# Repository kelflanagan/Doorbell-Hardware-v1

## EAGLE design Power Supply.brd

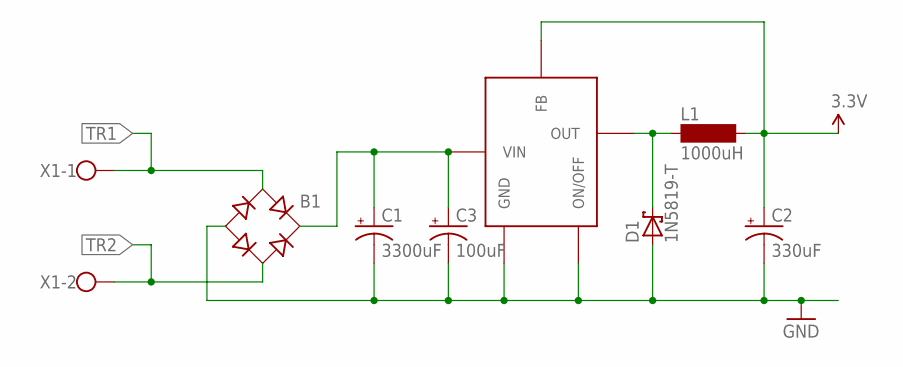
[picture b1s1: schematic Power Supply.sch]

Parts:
B1: DBDB101G; DB
C1: 3300uF; E7,5-18
C2: 330uF; E5-8,5
C3: 100uF; E5-8,5
D1: 1N5819-T; DO41-7.6
L1: 1000uH; BS11
U$1: LM2575; LINEAR-TECHNOLOGY_TO220-5
X1: W237-102

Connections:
3.3V: C2.+, L1.2, U$1.FB
GND: B1.-, C1.-, C2.-, C3.-, D1.A, U$1.GND, U$1.ON/OFF
unnamed: D1.C, L1.1, U$1.OUT
unnamed: B1.+, C1.+, C3.+, U$1.VIN
TR1: B1.AC1, X1.1
TR2: B1.AC2, X1.2

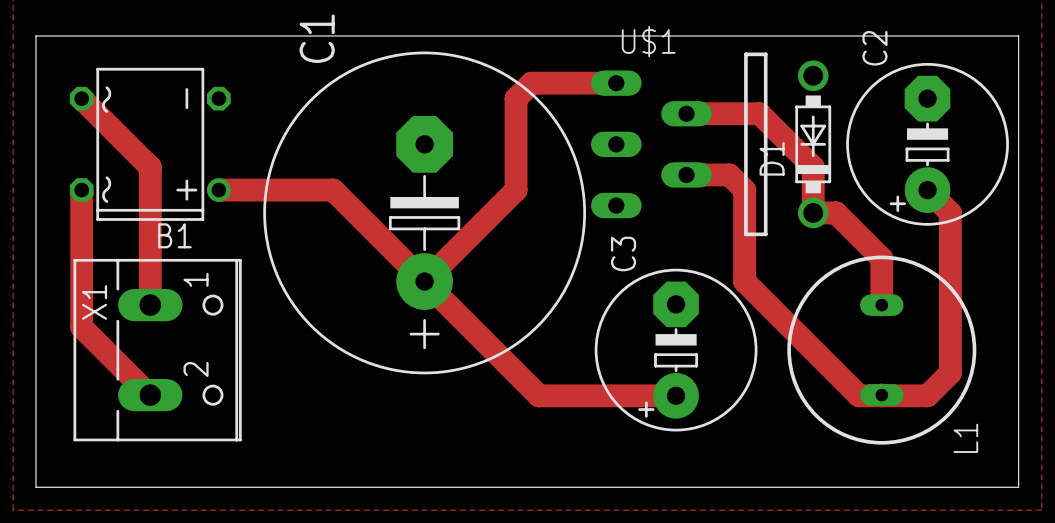
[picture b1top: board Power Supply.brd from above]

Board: 2 copper layers, 54.6 x 25.1 mm, 8 parts (0 on the bottom side), 6 nets.

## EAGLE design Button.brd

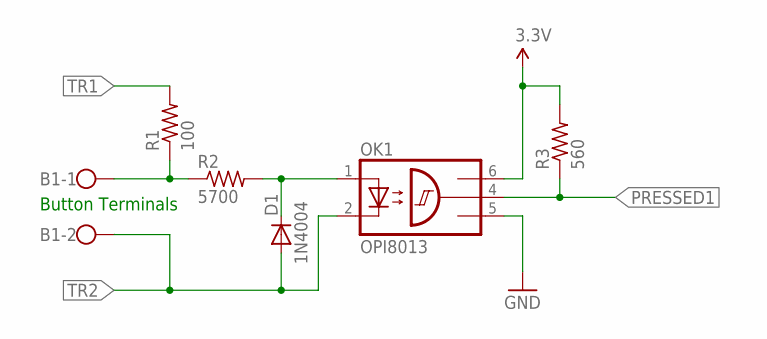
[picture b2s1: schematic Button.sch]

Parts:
B1: W237-102
D1: 1N4004; DO41-10
OK1: OPI8013; DIL06
R1: 100; P0817/22
R2: 5700; 0207/12
R3: 560; 0207/7

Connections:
3.3V: OK1.6 (VCC), R3.2
B1: B1.1, R1.1, R2.1
GND: OK1.5 (GND)
unnamed: D1.C, OK1.1 (A), R2.2
PRESSED1: OK1.4 (OUT), R3.1
TR1: R1.2
TR2: B1.2, D1.A, OK1.2 (C)

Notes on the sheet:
Button Terminals

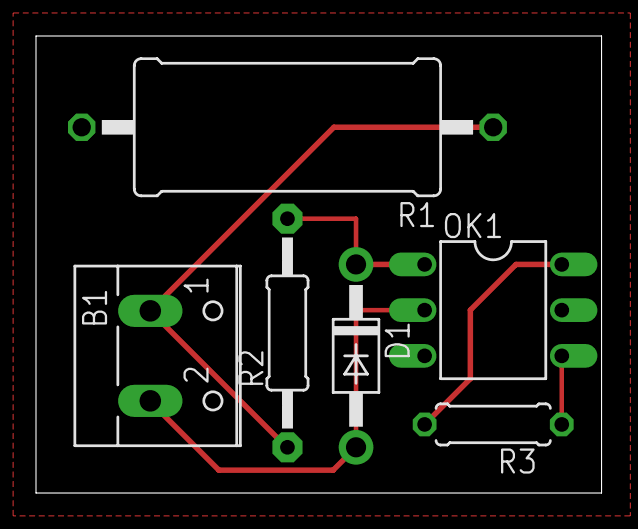
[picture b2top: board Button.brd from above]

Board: 2 copper layers, 31.4 x 25.4 mm, 6 parts (0 on the bottom side), 5 nets.

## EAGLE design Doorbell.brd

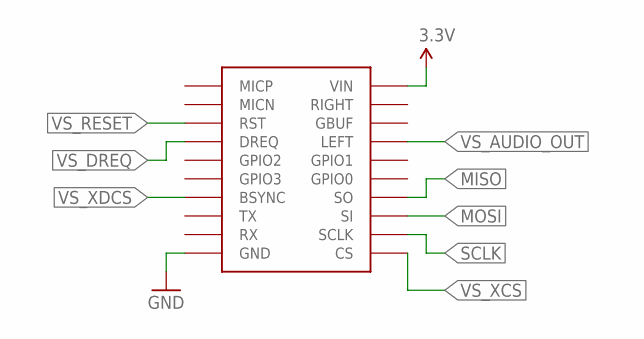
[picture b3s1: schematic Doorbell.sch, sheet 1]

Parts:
U$3: VS1011E; ADAFRUIT_1X10-BIG

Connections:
3.3V: U$3.VIN; also elsewhere on the board
GND: U$3.GND; also elsewhere on the board
MISO: U$3.SO; also elsewhere on the board
MOSI: U$3.SI; also elsewhere on the board
SCLK: U$3.SCLK; also elsewhere on the board
VS_AUDIO_OUT: U$3.LEFT; also elsewhere on the board
VS_DREQ: U$3.DREQ; also elsewhere on the board
VS_RESET: U$3.RST; also elsewhere on the board
VS_XCS: U$3.CS; also elsewhere on the board
VS_XDCS: U$3.BSYNC; also elsewhere on the board

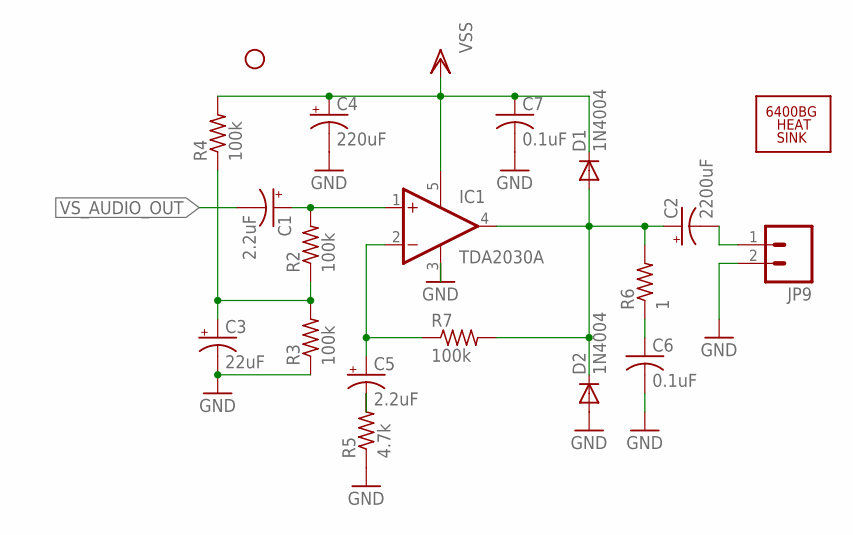
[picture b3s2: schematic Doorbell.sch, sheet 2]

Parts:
C1, C5: 2.2uF; E2-5
C2: 2200uF; E7,5-16
C3: 22uF; E2-5
C4: 220uF; E5-10,5
C6, C7: 0.1uF; C025-030X050
D1, D2: 1N4004; DO41-10
IC1: TDA2030A; CB360
JP7: STAND-OFF
JP9: M025MM; SCREWTERMINAL-5MM-2
R2, R3, R4, R7: 100k; 0207/7
R5: 4.7k; 0207/7
R6: 1; 0207/7
U$1: 6400BG_HEATSINK

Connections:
GND: C3.-, C4.-, C6.2, C7.2, D2.A, IC1.3 (GND), JP9.2, R3.1, R5.1; also elsewhere on the board
unnamed: C6.1, R6.1
unnamed: C2.+, D1.A, D2.C, IC1.4 (OUT), R6.2, R7.2
unnamed: C5.-, R5.2
unnamed: C5.+, IC1.2 (-IN), R7.1
unnamed: C1.+, IC1.1 (+IN), R2.2
unnamed: C3.+, R2.1, R3.2, R4.1
unnamed: C2.-, JP9.1
VSS: C4.+, C7.1, D1.C, IC1.5 (V+), R4.2; also elsewhere on the board
VS_AUDIO_OUT: C1.-; also elsewhere on the board

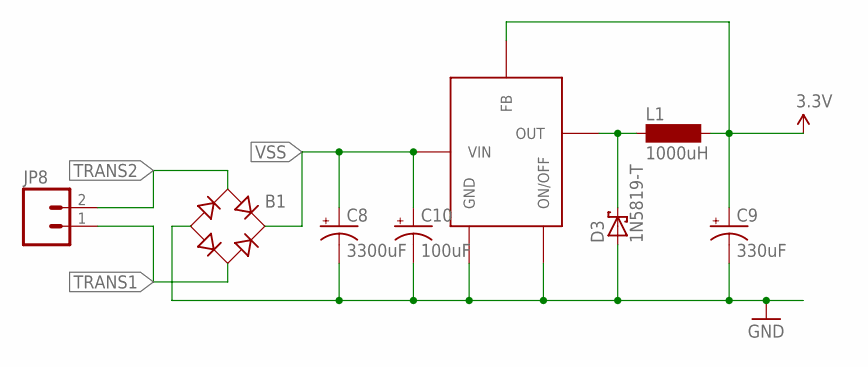
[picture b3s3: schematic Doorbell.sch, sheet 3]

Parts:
B1: DBDB101G; DB
C8: 3300uF; E7,5-18
C9: 330uF; E5-8,5
C10: 100uF; E5-8,5
D3: 1N5819-T; DO41-7.6
JP8: M025MM; SCREWTERMINAL-5MM-2
L1: 1000uH; BS11
U$2: LM2575; LINEAR-TECHNOLOGY_TO220-5

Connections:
3.3V: C9.+, L1.2, U$2.FB; also elsewhere on the board
GND: B1.-, C8.-, C9.-, C10.-, D3.A, U$2.GND, U$2.ON/OFF; also elsewhere on the board
unnamed: D3.C, L1.1, U$2.OUT
TRANS1: B1.AC2, JP8.1; also elsewhere on the board
TRANS2: B1.AC1, JP8.2; also elsewhere on the board
VSS: B1.+, C8.+, C10.+, U$2.VIN; also elsewhere on the board

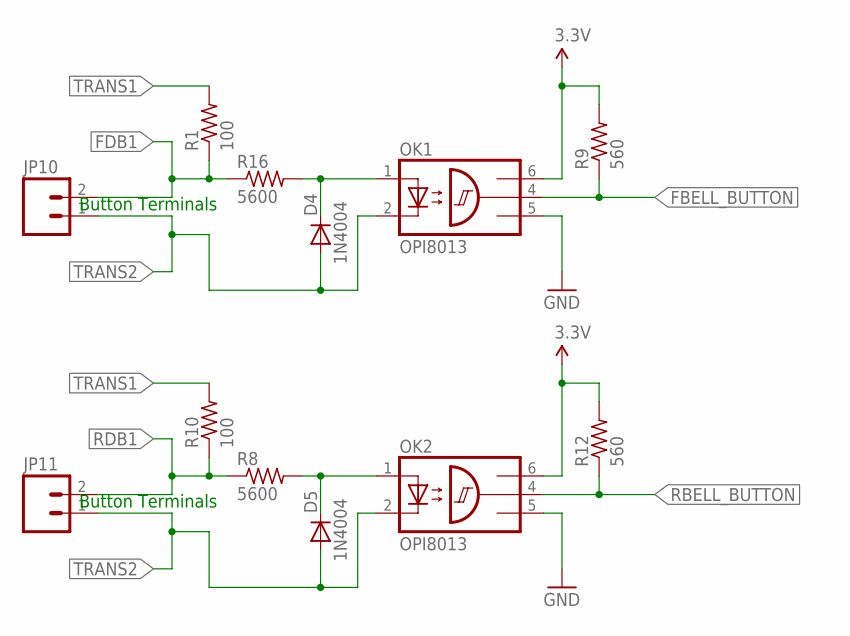
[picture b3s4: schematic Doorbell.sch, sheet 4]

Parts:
D4, D5: 1N4004; DO41-10
JP10, JP11: M025MM; SCREWTERMINAL-5MM-2
OK1, OK2: OPI8013; DIL06
R1, R10: 100; P0817/22
R8, R16: 5600; 0207/12
R9, R12: 560; 0207/7

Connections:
3.3V: OK1.6 (VCC), OK2.6 (VCC), R9.2, R12.2; also elsewhere on the board
FBELL_BUTTON: OK1.4 (OUT), R9.1; also elsewhere on the board
FDB1: JP10.2, R1.1, R16.1
GND: OK1.5 (GND), OK2.5 (GND); also elsewhere on the board
unnamed: D4.C, OK1.1 (A), R16.2
unnamed: D5.C, OK2.1 (A), R8.2
RBELL_BUTTON: OK2.4 (OUT), R12.1; also elsewhere on the board
RDB1: JP11.2, R8.1, R10.1
TRANS1: R1.2, R10.2; also elsewhere on the board
TRANS2: D4.A, D5.A, JP10.1, JP11.1, OK1.2 (C), OK2.2 (C); also elsewhere on the board

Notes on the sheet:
Button Terminals

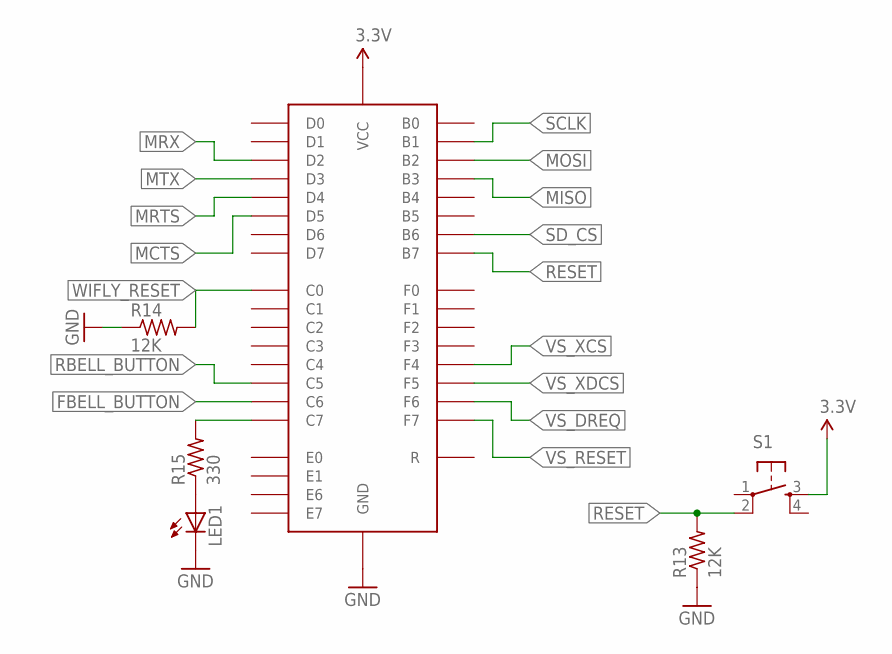
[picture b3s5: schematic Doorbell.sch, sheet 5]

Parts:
LED1: LED3MM
R13, R14: 12K; 0207/7
R15: 330; 0207/7
S1: TAC_SWITCHPTH; TACTILE-PTH
U$4: AT90USB1286AT90USB1286BREAKOUT; ADAFRUIT_1X10-BIG

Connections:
3.3V: S1.3, U$4.VCC; also elsewhere on the board
FBELL_BUTTON: U$4.C6; also elsewhere on the board
GND: LED1.K (C), R13.1, R14.1, U$4.GND; also elsewhere on the board
MCTS: U$4.D5; also elsewhere on the board
MISO: U$4.B3; also elsewhere on the board
MOSI: U$4.B2; also elsewhere on the board
MRTS: U$4.D4; also elsewhere on the board
MRX: U$4.D2; also elsewhere on the board
MTX: U$4.D3; also elsewhere on the board
unnamed: R15.2, U$4.C7
unnamed: LED1.A, R15.1
RBELL_BUTTON: U$4.C5; also elsewhere on the board
RESET: R13.2, S1.2, U$4.B7
SCLK: U$4.B1; also elsewhere on the board
SD_CS: U$4.B6; also elsewhere on the board
VS_DREQ: U$4.F6; also elsewhere on the board
VS_RESET: U$4.F7; also elsewhere on the board
VS_XCS: U$4.F4; also elsewhere on the board
VS_XDCS: U$4.F5; also elsewhere on the board
WIFLY_RESET: R14.2, U$4.C0; also elsewhere on the board

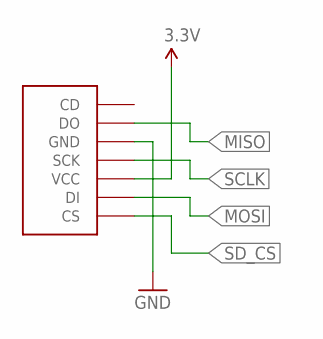
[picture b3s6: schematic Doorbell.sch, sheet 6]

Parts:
U$5: MICROSDMICROSDBREAKOUT; ADAFRUIT_1X08-BIG

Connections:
3.3V: U$5.VCC; also elsewhere on the board
GND: U$5.GND; also elsewhere on the board
MISO: U$5.DO; also elsewhere on the board
MOSI: U$5.DI; also elsewhere on the board
SCLK: U$5.SCK; also elsewhere on the board
SD_CS: U$5.CS; also elsewhere on the board

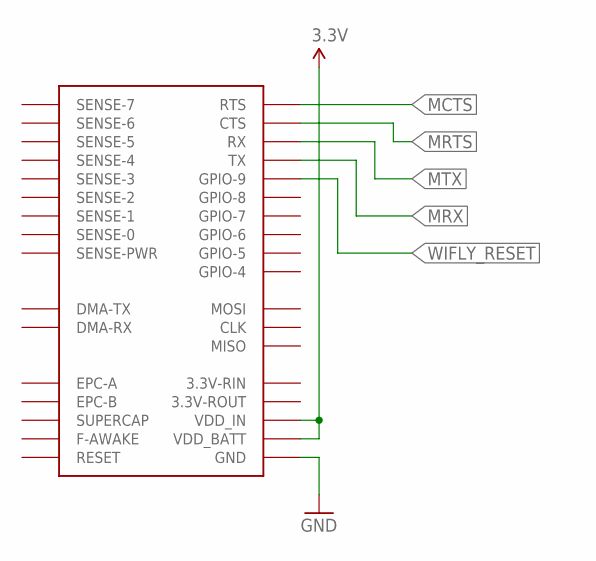
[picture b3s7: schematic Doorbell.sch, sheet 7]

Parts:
U$6: WIFLY_BREAKOUT; SPARKFUN_1X17

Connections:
3.3V: U$6.VDD_BATT, U$6.VDD_IN; also elsewhere on the board
GND: U$6.GND; also elsewhere on the board
MCTS: U$6.RTS; also elsewhere on the board
MRTS: U$6.CTS; also elsewhere on the board
MRX: U$6.TX; also elsewhere on the board
MTX: U$6.RX; also elsewhere on the board
WIFLY_RESET: U$6.GPIO-9; also elsewhere on the board

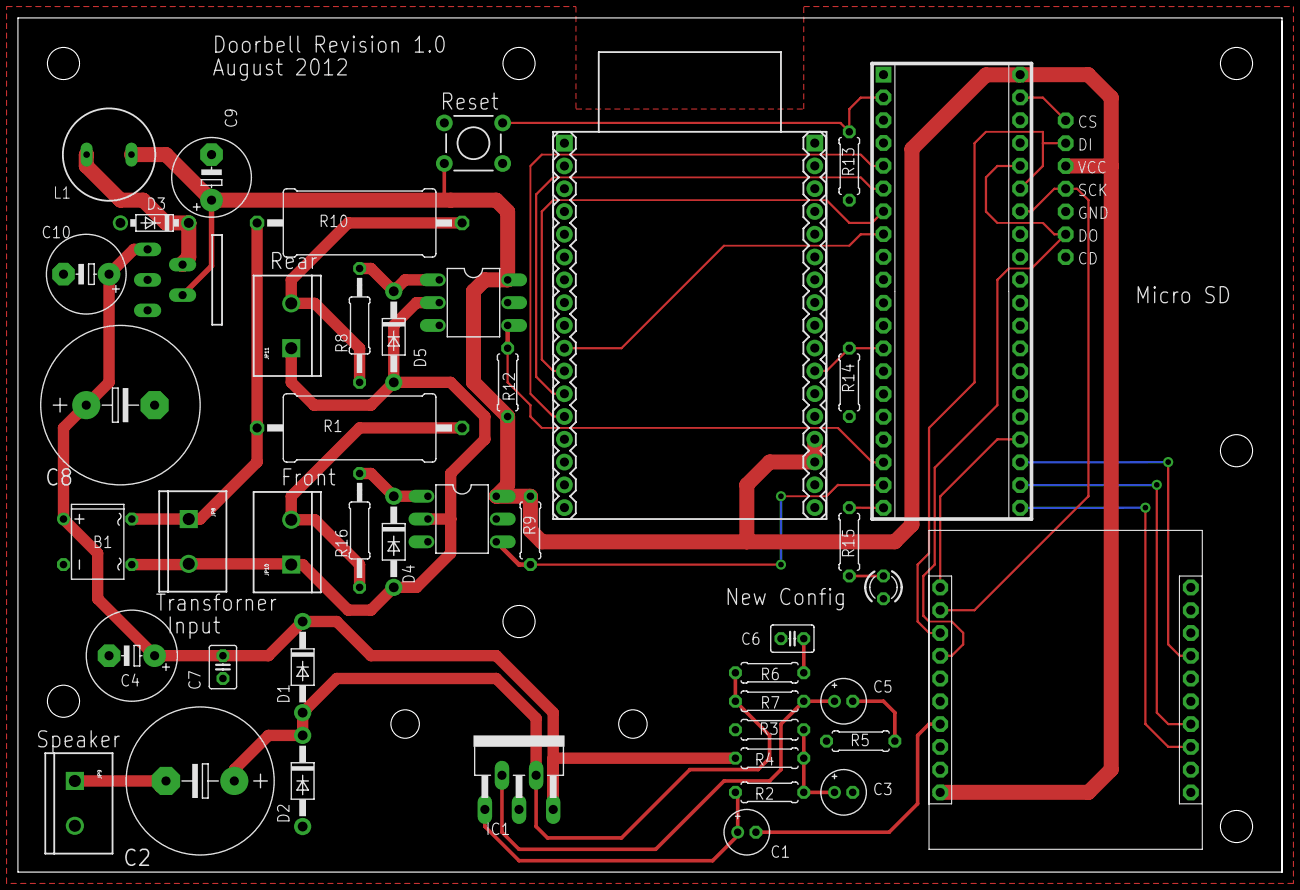
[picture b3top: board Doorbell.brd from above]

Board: 2 copper layers, 141.0 x 95.2 mm, 54 parts (0 on the bottom side), 36 nets.

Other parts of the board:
JP1, JP2, JP3, JP4, JP5, JP6: STAND-OFF

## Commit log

2016-05-04 Frist commit

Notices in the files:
parts and their libraries:
SparkFun-Aesthetics: Licensing: CC v3.0 Share-Alike You are welcome to use this library for commercial purposes.
